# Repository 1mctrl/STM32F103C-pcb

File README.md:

# STM32F103C Custom PCB Design

A custom PCB project for the STM32F103C microcontroller, designed using KiCad.

## 📁 Project Contents

- `stm.kicad_sch` — schematic file  
- `stm.kicad_pcb` — PCB layout  
- `stm.csv`, `*-pos.csv` — BOM and component position files  
- `stm32f103c-gerbers.zip` — production-ready Gerber files  
- `stm32f103c.step` — 3D model of the MCU  
- `.kicad_pro`, `.kicad_prl` — KiCad project config files  

---

## 🧩 Screenshots

### 🔌 Schematic

### 🧷 PCB Layout

### 🧱 3D View

### 📐 Footprint Assignment Table

---

## 🛠 Software

- Designed with [KiCad ](https://kicad.org/)

---

## 🏭 Fabrication

The `stm32f103c-gerbers.zip` archive contains all files required for PCB manufacturing (e.g., JLCPCB, PCBWay).

> ⚠️ No sponsorships, affiliate links, or promotional mentions are accepted in this repository.
---

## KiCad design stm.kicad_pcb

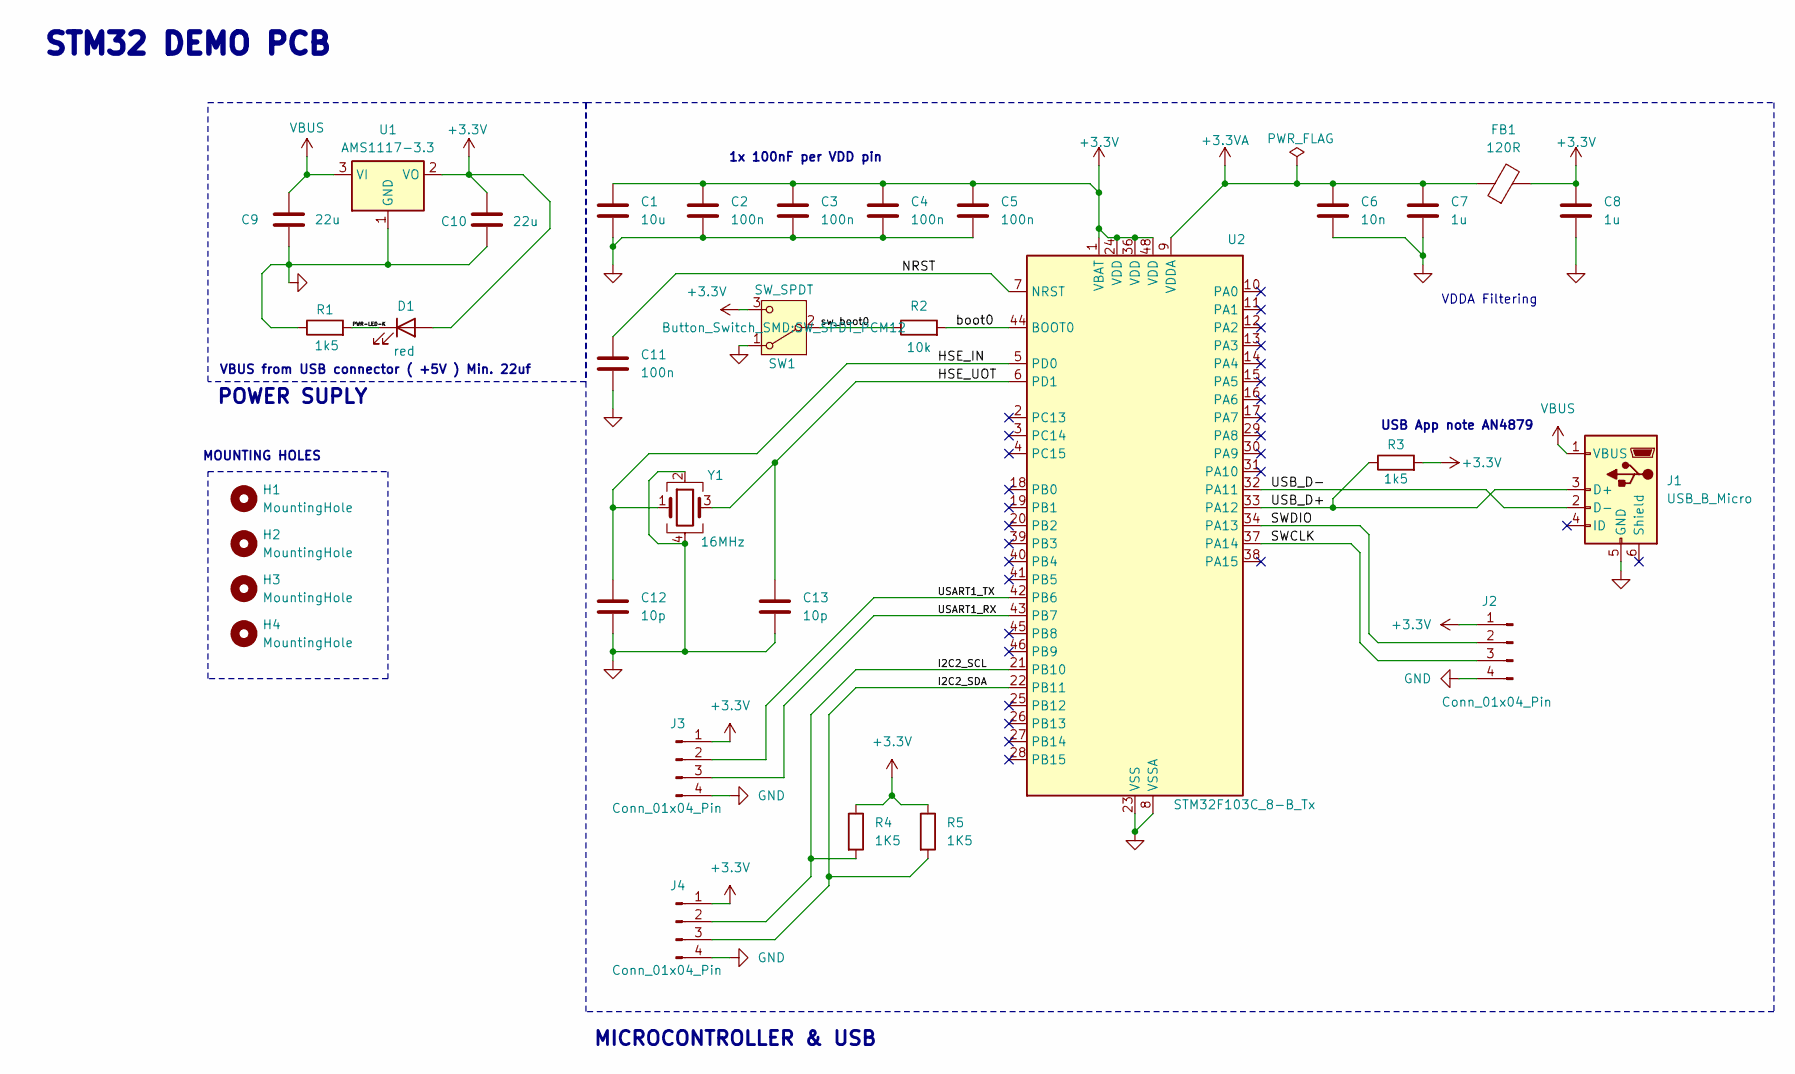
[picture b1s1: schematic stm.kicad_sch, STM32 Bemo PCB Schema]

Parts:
C1: 10u; C_0603_1608Metric
C2, C3, C4, C5, C11: 100n; C_0402_1005Metric
C6: 10n; C_0402_1005Metric
C7, C8: 1u; C_0402_1005Metric
C9, C10: 22u; C_0805_2012Metric
C12, C13: 10p; C_0402_1005Metric
D1: red; LED_0603_1608Metric
FB1: 120R; L_0603_1608Metric
H1, H2, H3, H4: MountingHole; MountingHole_2.2mm_M2
J1: USB_B_Micro; USB_Micro-B_Wuerth_629105150521
J2, J3, J4: Conn_01x04_Pin; PinHeader_1x04_P2.54mm_Vertical
R1, R3: 1k5; R_0402_1005Metric
R2: 10k; R_0402_1005Metric
R4, R5: 1K5; R_0402_1005Metric
SW1: SW_SPDT; SW_SPDT_PCM12
U1: AMS1117-3.3; SOT-223-3_TabPin2
U2: STM32F103C_8-B_Tx; LQFP-48_7x7mm_P0.5mm
Y1: 16MHz; Crystal_SMD_3225-4Pin_3.2x2.5mm

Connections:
+3.3V: C1.1, C2.1, C3.1, C4.1, C5.1, C8.1, C10.1, D1.2 (A), FB1.2, J2.1, J3.1, J4.1, R3.2, R4.1, R5.1, SW1.3 (C), U1.2 (VO), U2.1 (VBAT), U2.24 (VDD), U2.36 (VDD), U2.48 (VDD)
+3.3VA: C6.1, C7.1, FB1.1, U2.9 (VDDA)
/HSE_IN: C12.1, U2.5 (PD0), Y1.1
/HSE_UOT: C13.1, U2.6 (PD1), Y1.3
/I2C2_SCL: J4.2, R4.2, U2.21 (PB10)
/I2C2_SDA: J4.3, R5.2, U2.22 (PB11)
/NRST: C11.1, U2.7 (NRST)
/PWR-LED-K: D1.1 (K), R1.2
/SWCLK: J2.3, U2.37 (PA14)
/SWDIO: J2.2, U2.34 (PA13)
/USART1_RX: J3.3, U2.43 (PB7)
/USART1_TX: J3.2, U2.42 (PB6)
/USB_D+: J1.3 (D+), R3.1, U2.33 (PA12)
/USB_D-: J1.2 (D-), U2.32 (PA11)
/boot0: R2.2, U2.44 (BOOT0)
/sw_boot0: R2.1, SW1.2 (B)
GND: C1.2, C2.2, C3.2, C4.2, C5.2, C6.2, C7.2, C8.2, C9.2, C10.2, C11.2, C12.2, C13.2, J1.5 (GND), J2.4, J3.4, J4.4, R1.1, SW1.1 (A), U1.1 (GND), U2.8 (VSSA), U2.23 (VSS), U2.35 (VSS), U2.47 (VSS), Y1.2, Y1.4
VBUS: C9.1, J1.1 (VBUS), U1.3 (VI)

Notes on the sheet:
1x 100nF per VDD pin
VDDA Filtering
POWER SUPLY
STM32 DEMO PCB
MICROCONTROLLER & USB
USB App note AN4879
VBUS from USB connector ( +5V ) Min. 22uf
MOUNTING HOLES

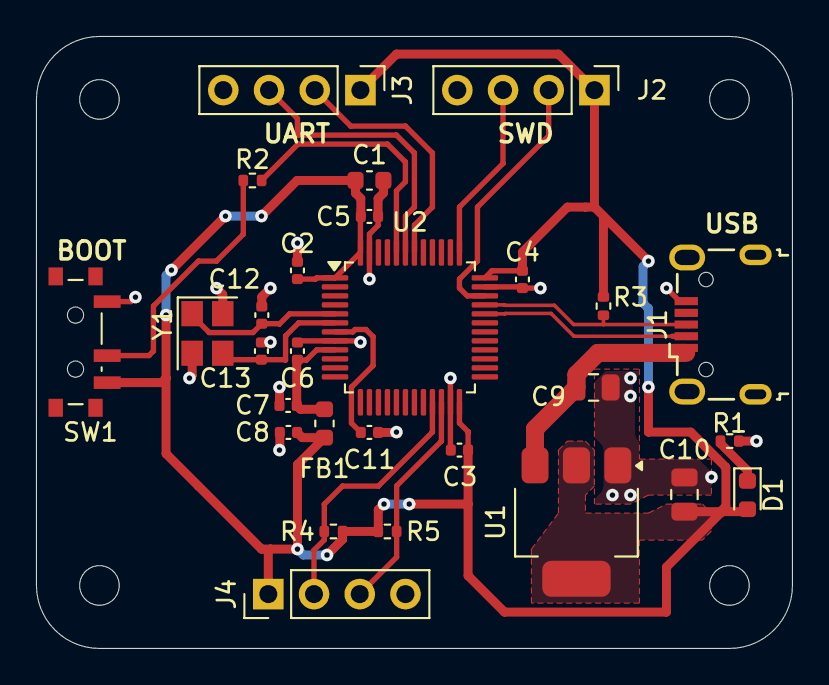
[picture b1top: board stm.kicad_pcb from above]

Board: 2 copper layers, 42.0 x 34.0 mm, 32 parts (0 on the bottom side), 18 nets.

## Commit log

2025-07-28 1st commit
2025-07-28 proto
2025-07-28 another
